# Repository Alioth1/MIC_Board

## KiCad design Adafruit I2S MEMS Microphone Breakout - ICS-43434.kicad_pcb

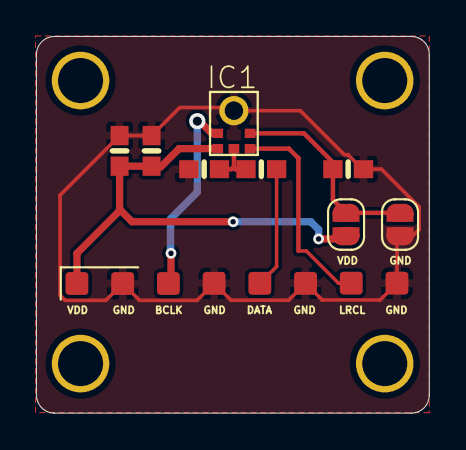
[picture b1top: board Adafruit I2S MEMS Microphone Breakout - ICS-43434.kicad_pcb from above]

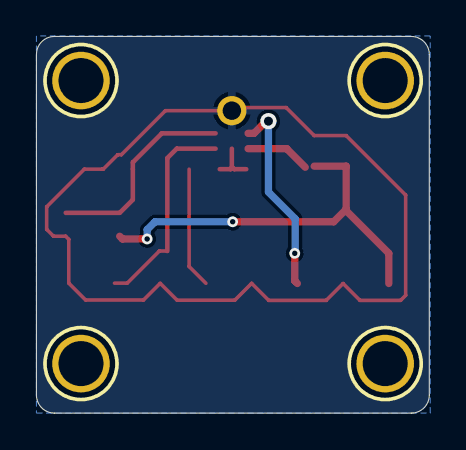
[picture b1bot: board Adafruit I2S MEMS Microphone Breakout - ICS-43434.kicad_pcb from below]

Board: 2 copper layers, 21.8 x 20.9 mm, 13 parts (4 on the bottom side), 7 nets.

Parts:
C2: 0.1uF; 0603-NO
C4: 1uF; 0603-NO
IC1: ICS-43434; SPH0645LM4H
J1: Conn_01x08_MountingPin; TestPoint_Bridge_Pitch2.54mm_8Pin
JP1, JP2: Jumper_2_Open; SolderJumper-2_P1.3mm_Open_RoundedPad1.0x1.5mm
R1: 68; 0603-NO
R2, R3: 47K; 0603-NO
U$6, U$6#2, U$12, U$12#2: MOUNTINGHOLE2.5; MOUNTINGHOLE_2.5_PLATED

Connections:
BCLK: IC1.4 (BCLK), J1.3
DATA: J1.5, R1.2
GND: C2.2, C4.2, IC1.3 (GND), J1.2, J1.4, J1.6, J1.8, JP1.1 (A), R2.1, R3.1
unnamed: IC1.6 (DATA), R1.1, R3.2
SELECT: IC1.2 (SELECT), JP1.2 (B), JP2.2 (B), R2.2
VDD: C2.1, C4.1, IC1.5 (VDD), J1.1, JP2.1 (A)
WS: IC1.1 (WS), J1.7
